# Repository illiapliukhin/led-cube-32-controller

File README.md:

# led-cube-32-controller
Controller system for 1–2 m³ RGB LED cubes built from hanging clocked-pixel strands (HD108, 16-bit, 27 kHz PWM).
- `ARCHITECTURE.md`: v2 architecture (RU summary + EN), with sizing for 32³…128³
- `calc/`: calculation scripts (`rgb_scaling.py`, plus v1 mono calcs)
- `hardware/main_v1`: main board (ESP32-S3 + 8 ports): schematic, PCB, fab
- `hardware/branch_v1`: branch board (16 strands): schematic
- `hardware/archive`: abandoned v1 mono tile (WIP, not DRC clean); `hardware/v15_baseline`: original mono board
- `docs/ARCHITECTURE_v1_mono.md`: phase-1 mono study (superseded)

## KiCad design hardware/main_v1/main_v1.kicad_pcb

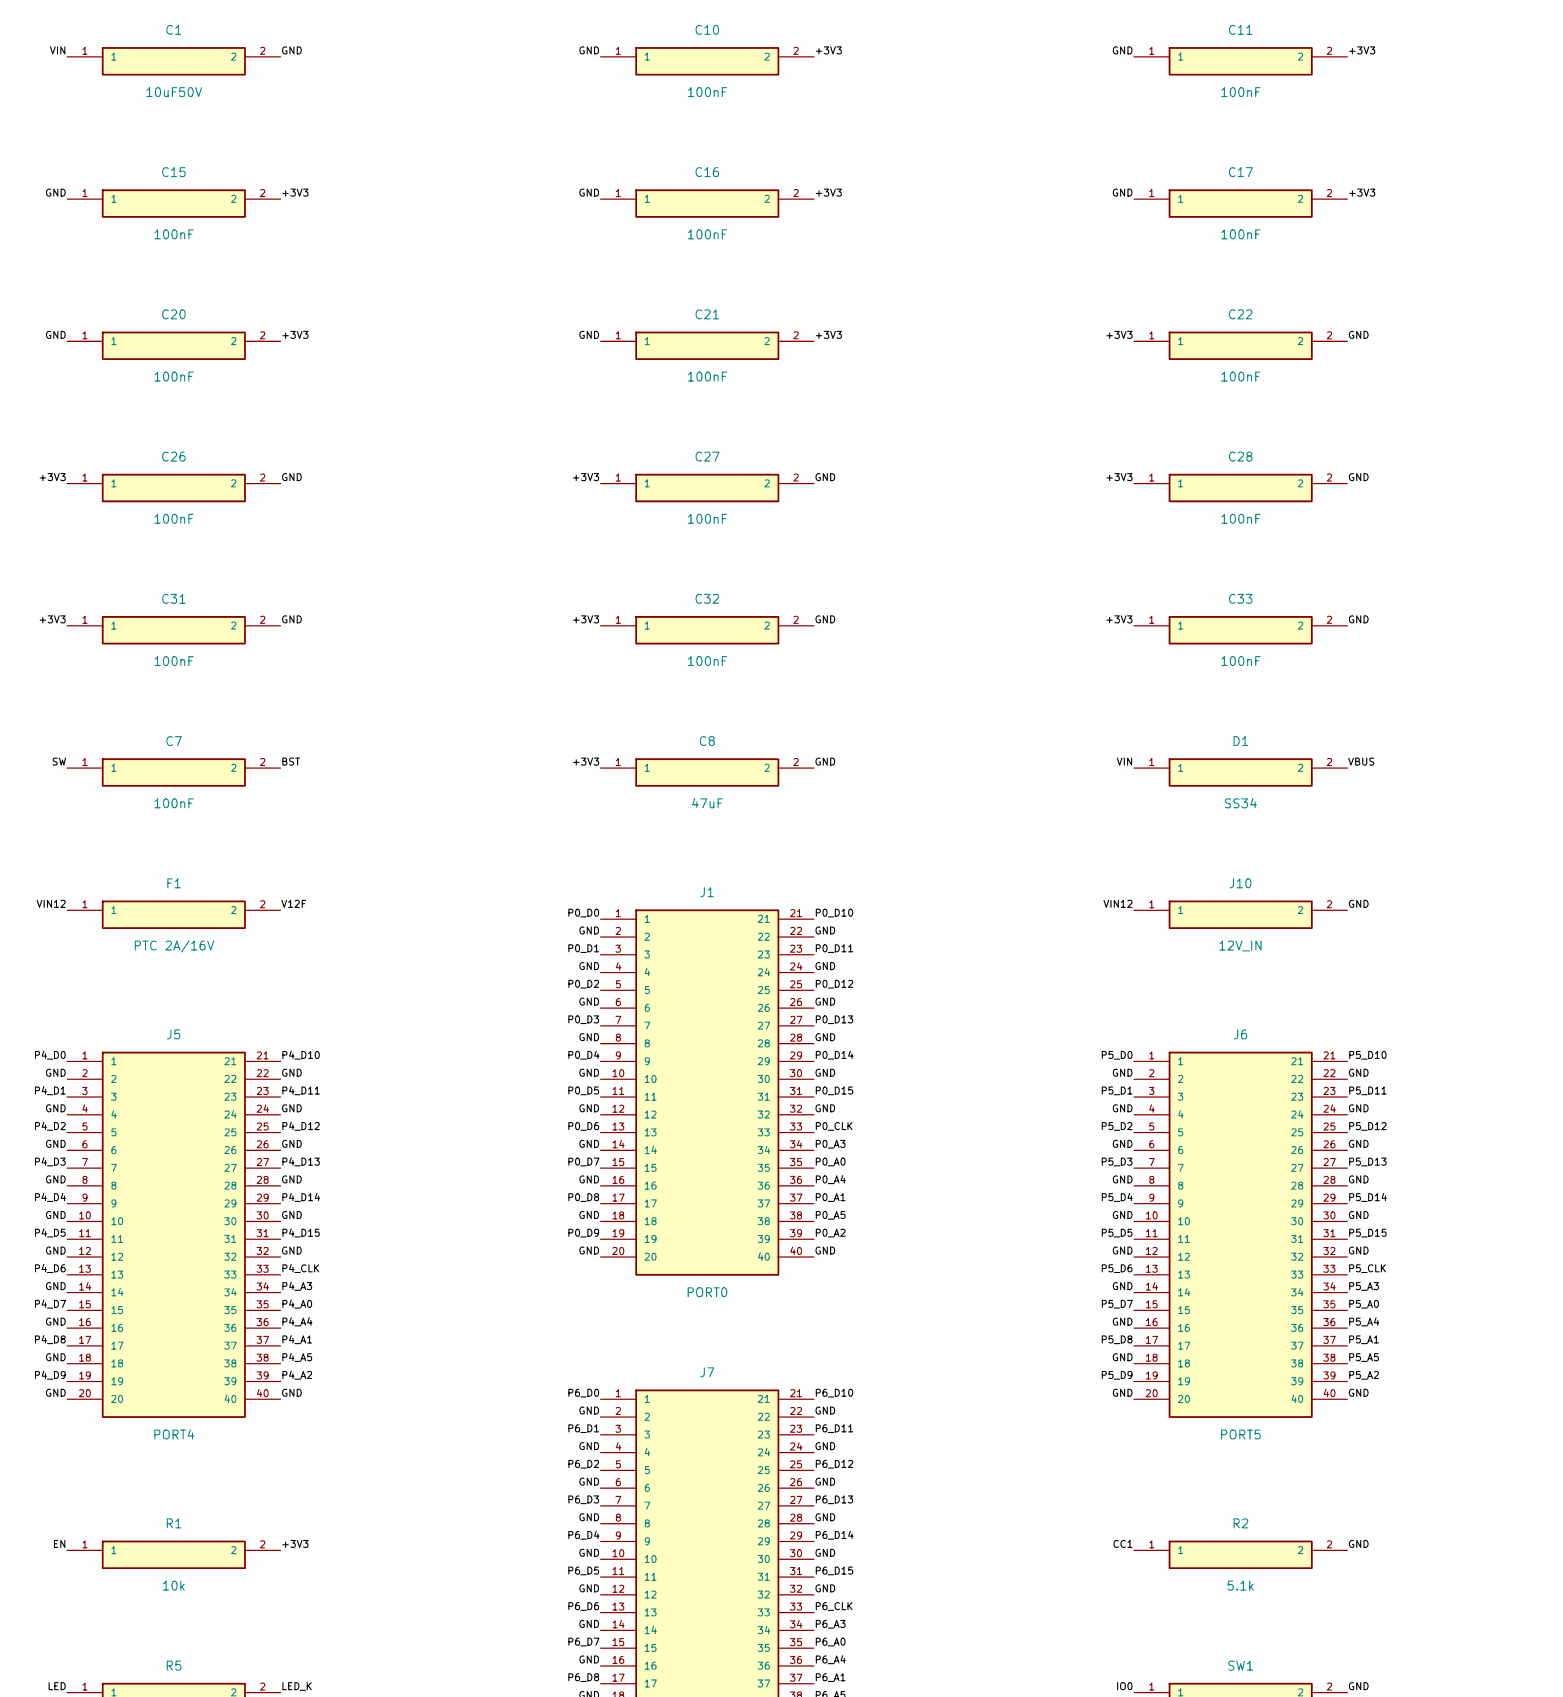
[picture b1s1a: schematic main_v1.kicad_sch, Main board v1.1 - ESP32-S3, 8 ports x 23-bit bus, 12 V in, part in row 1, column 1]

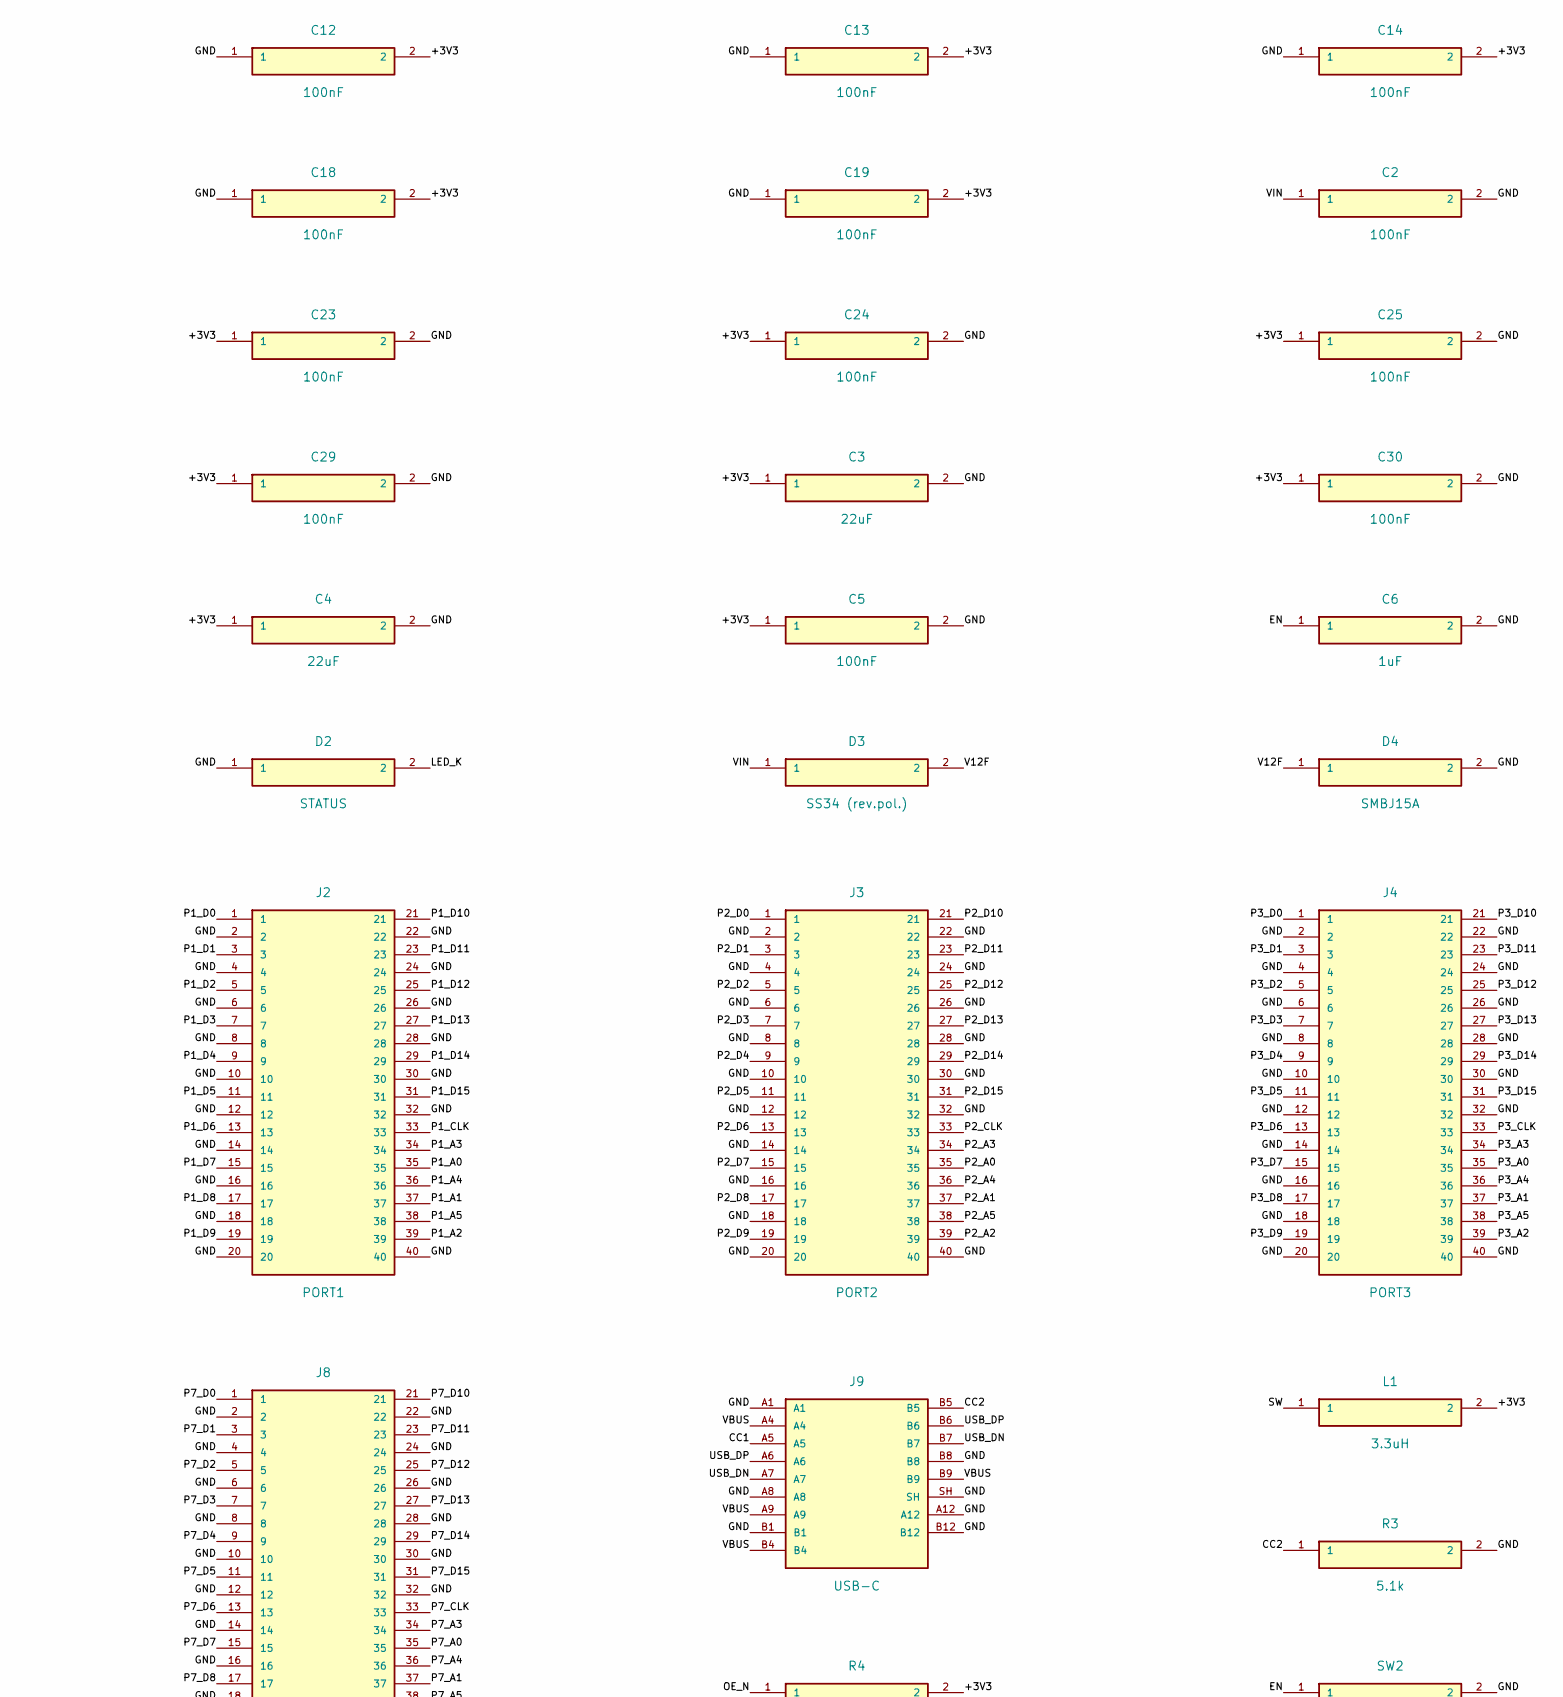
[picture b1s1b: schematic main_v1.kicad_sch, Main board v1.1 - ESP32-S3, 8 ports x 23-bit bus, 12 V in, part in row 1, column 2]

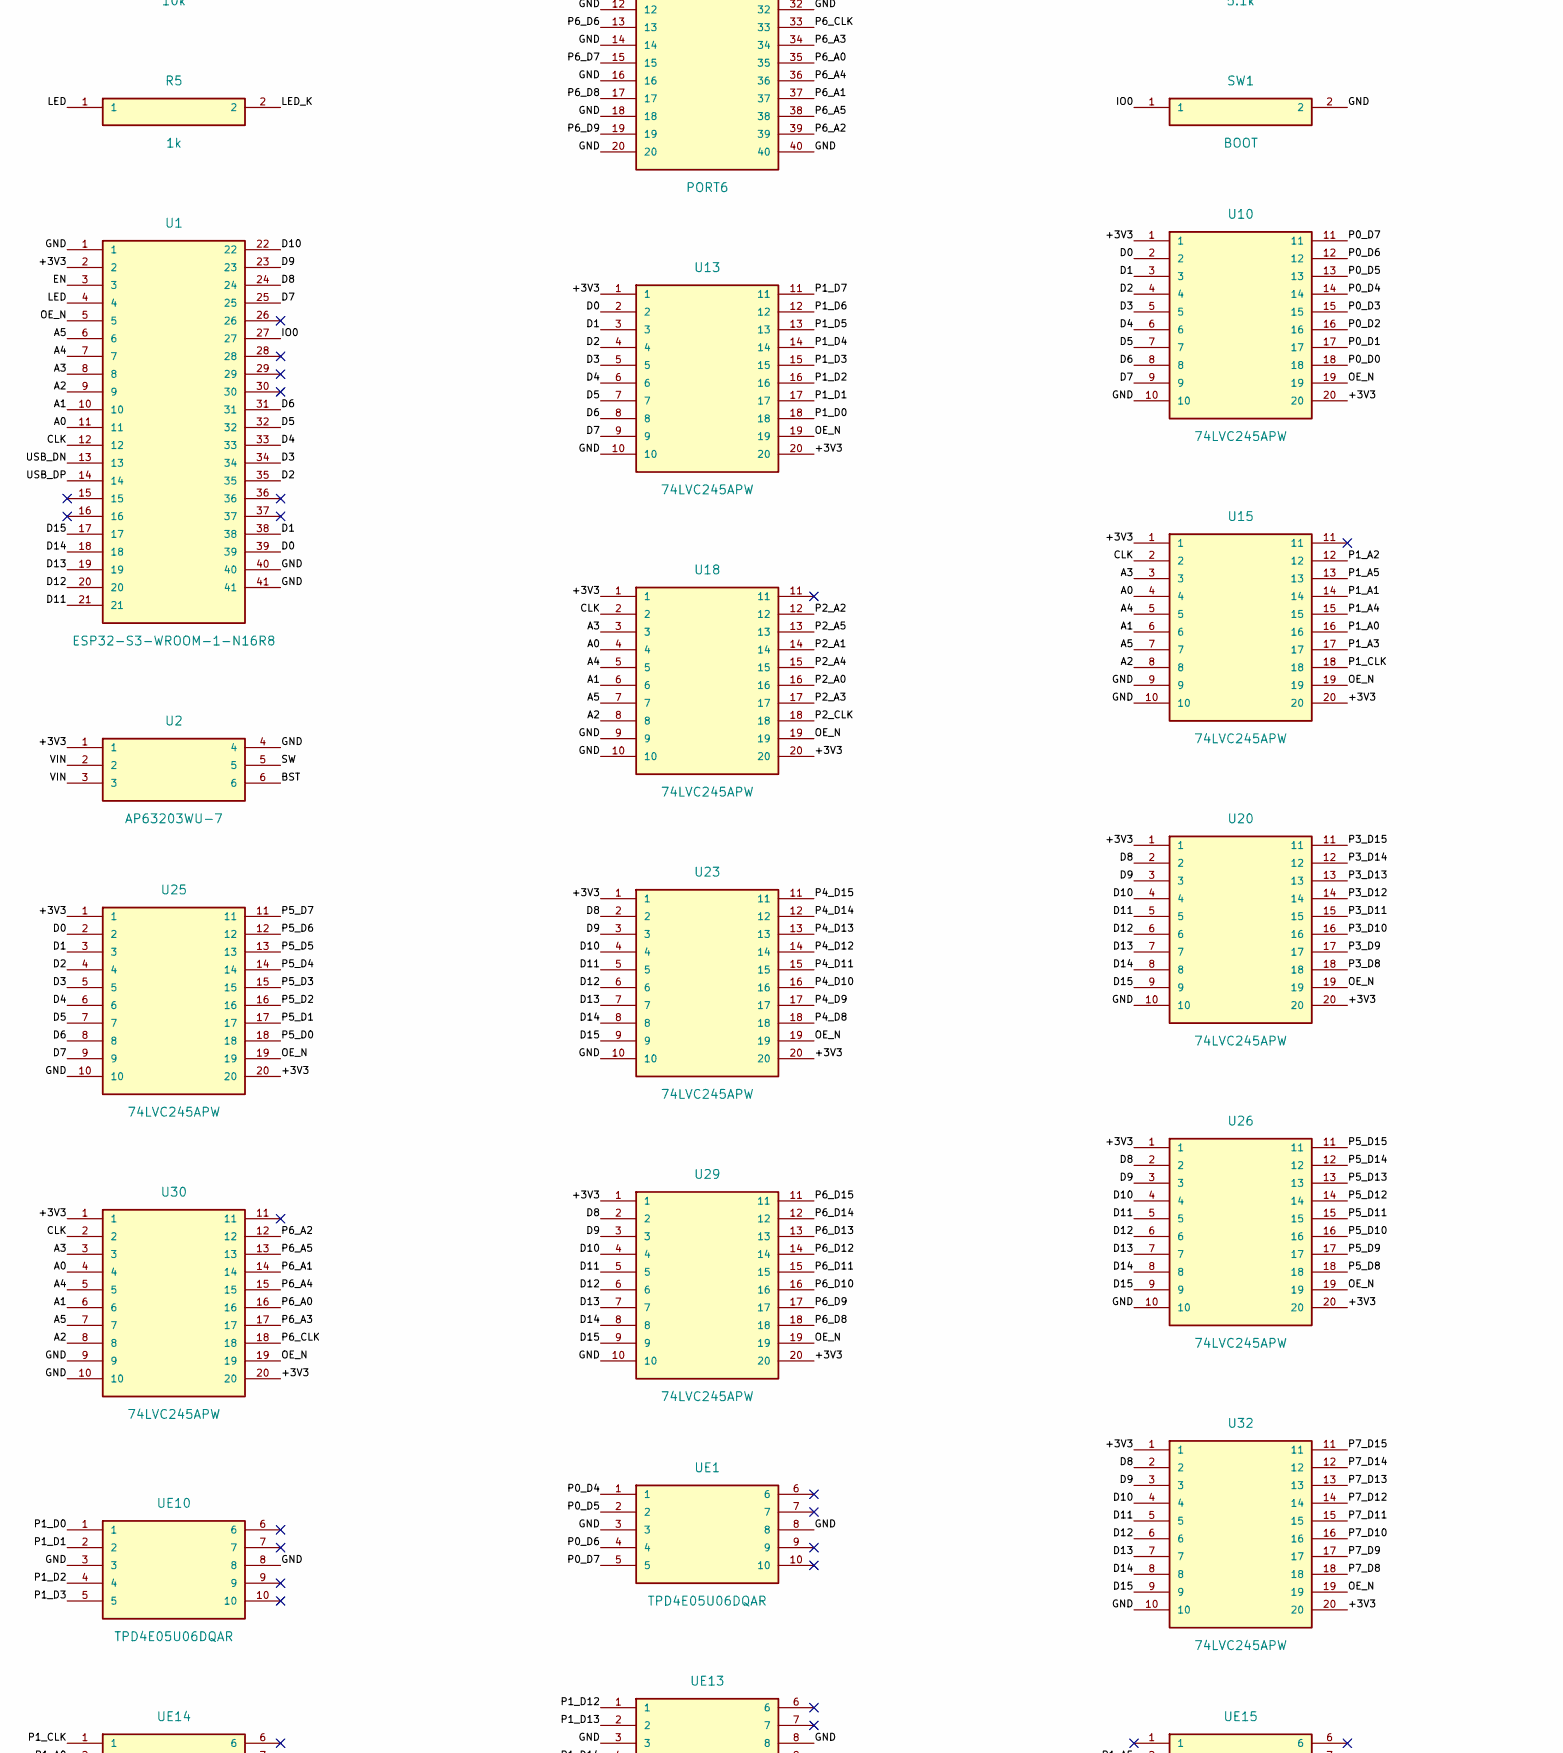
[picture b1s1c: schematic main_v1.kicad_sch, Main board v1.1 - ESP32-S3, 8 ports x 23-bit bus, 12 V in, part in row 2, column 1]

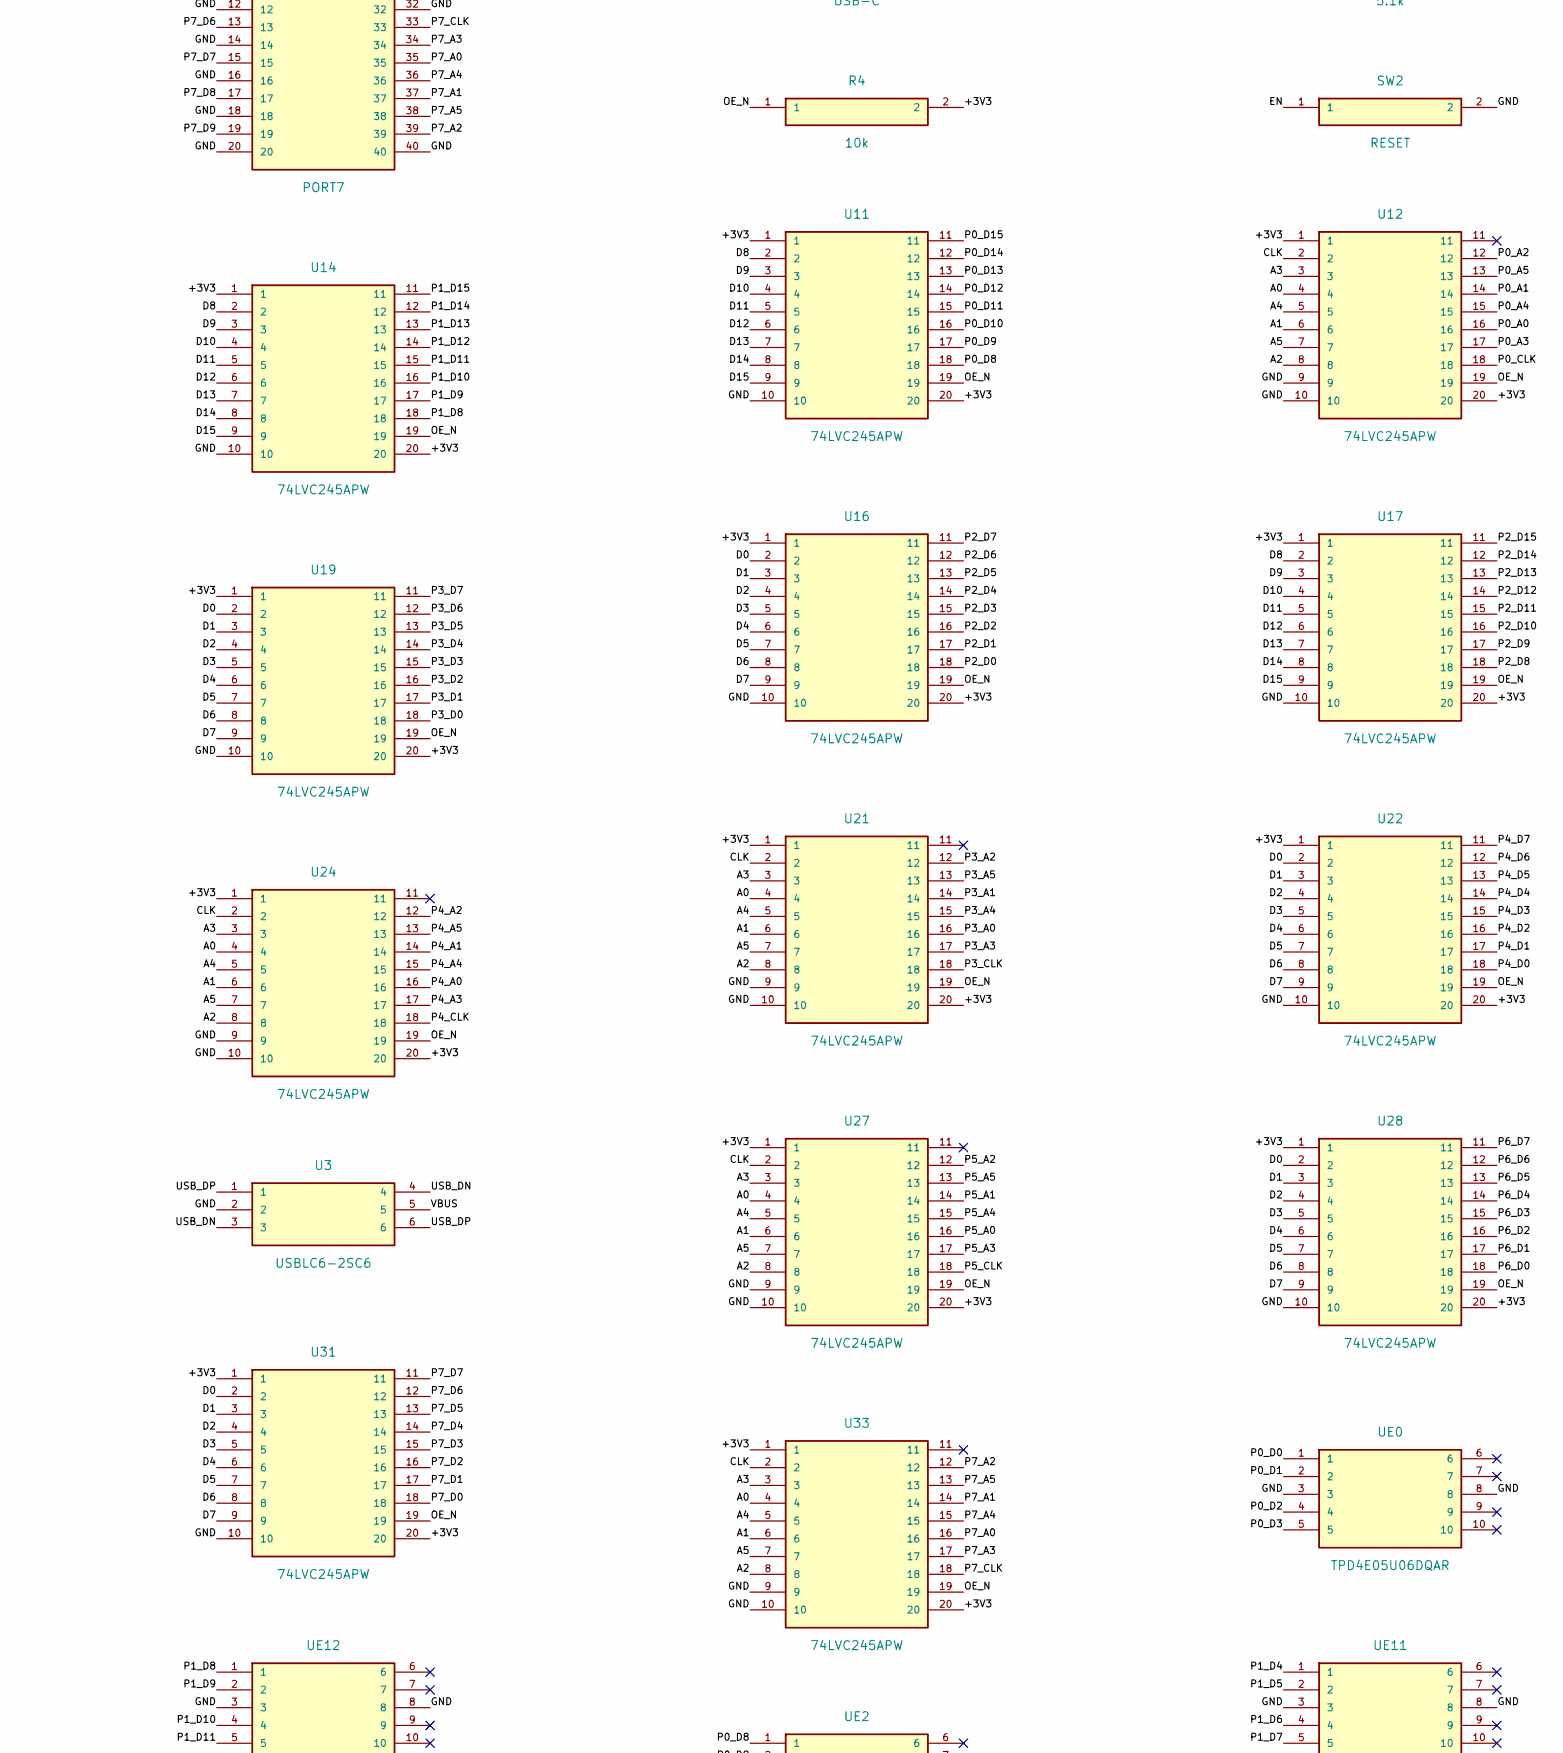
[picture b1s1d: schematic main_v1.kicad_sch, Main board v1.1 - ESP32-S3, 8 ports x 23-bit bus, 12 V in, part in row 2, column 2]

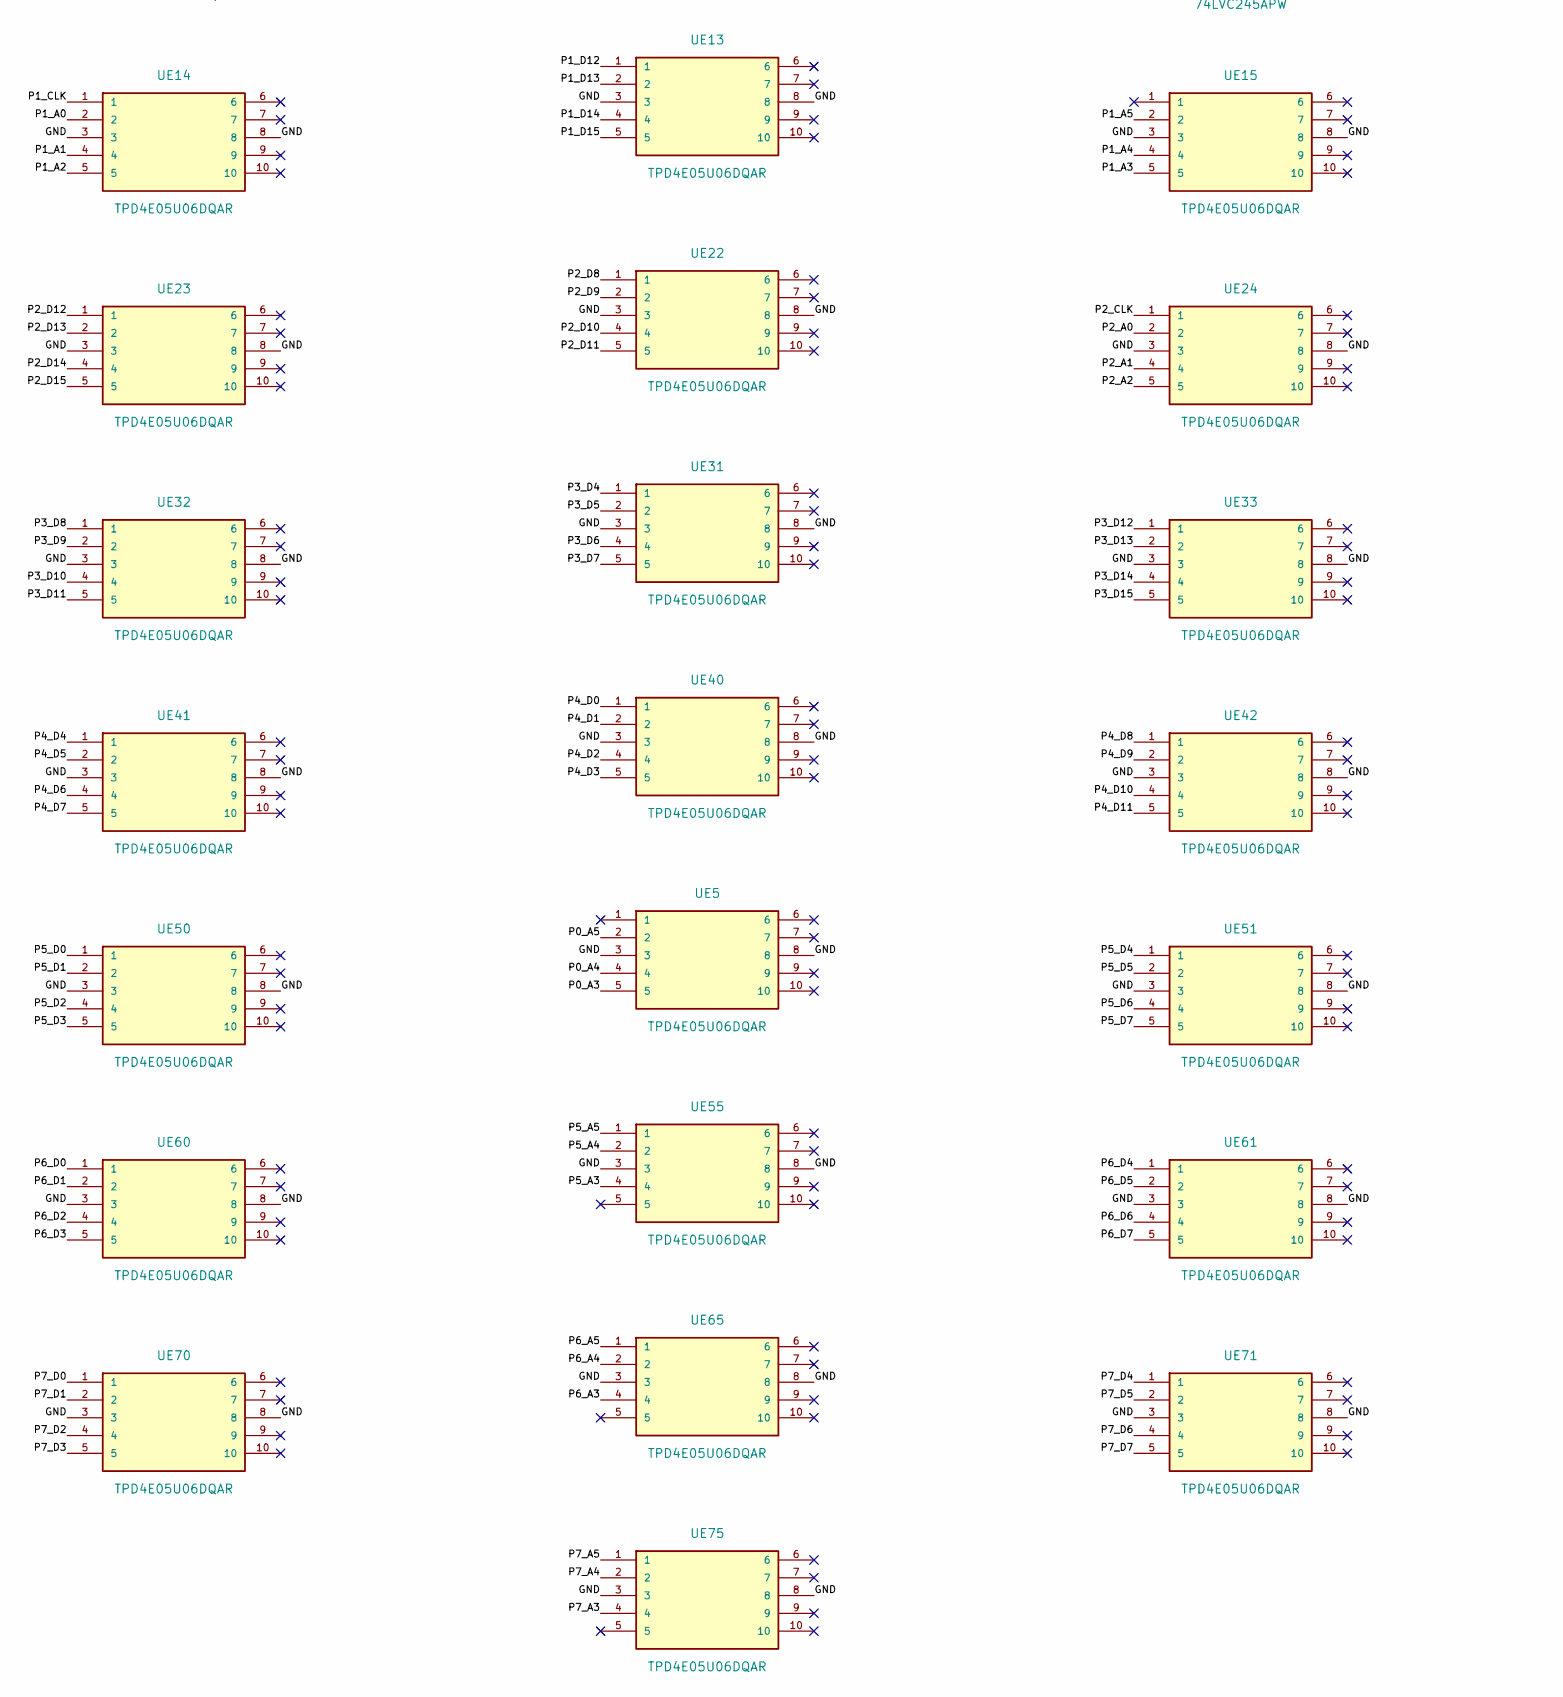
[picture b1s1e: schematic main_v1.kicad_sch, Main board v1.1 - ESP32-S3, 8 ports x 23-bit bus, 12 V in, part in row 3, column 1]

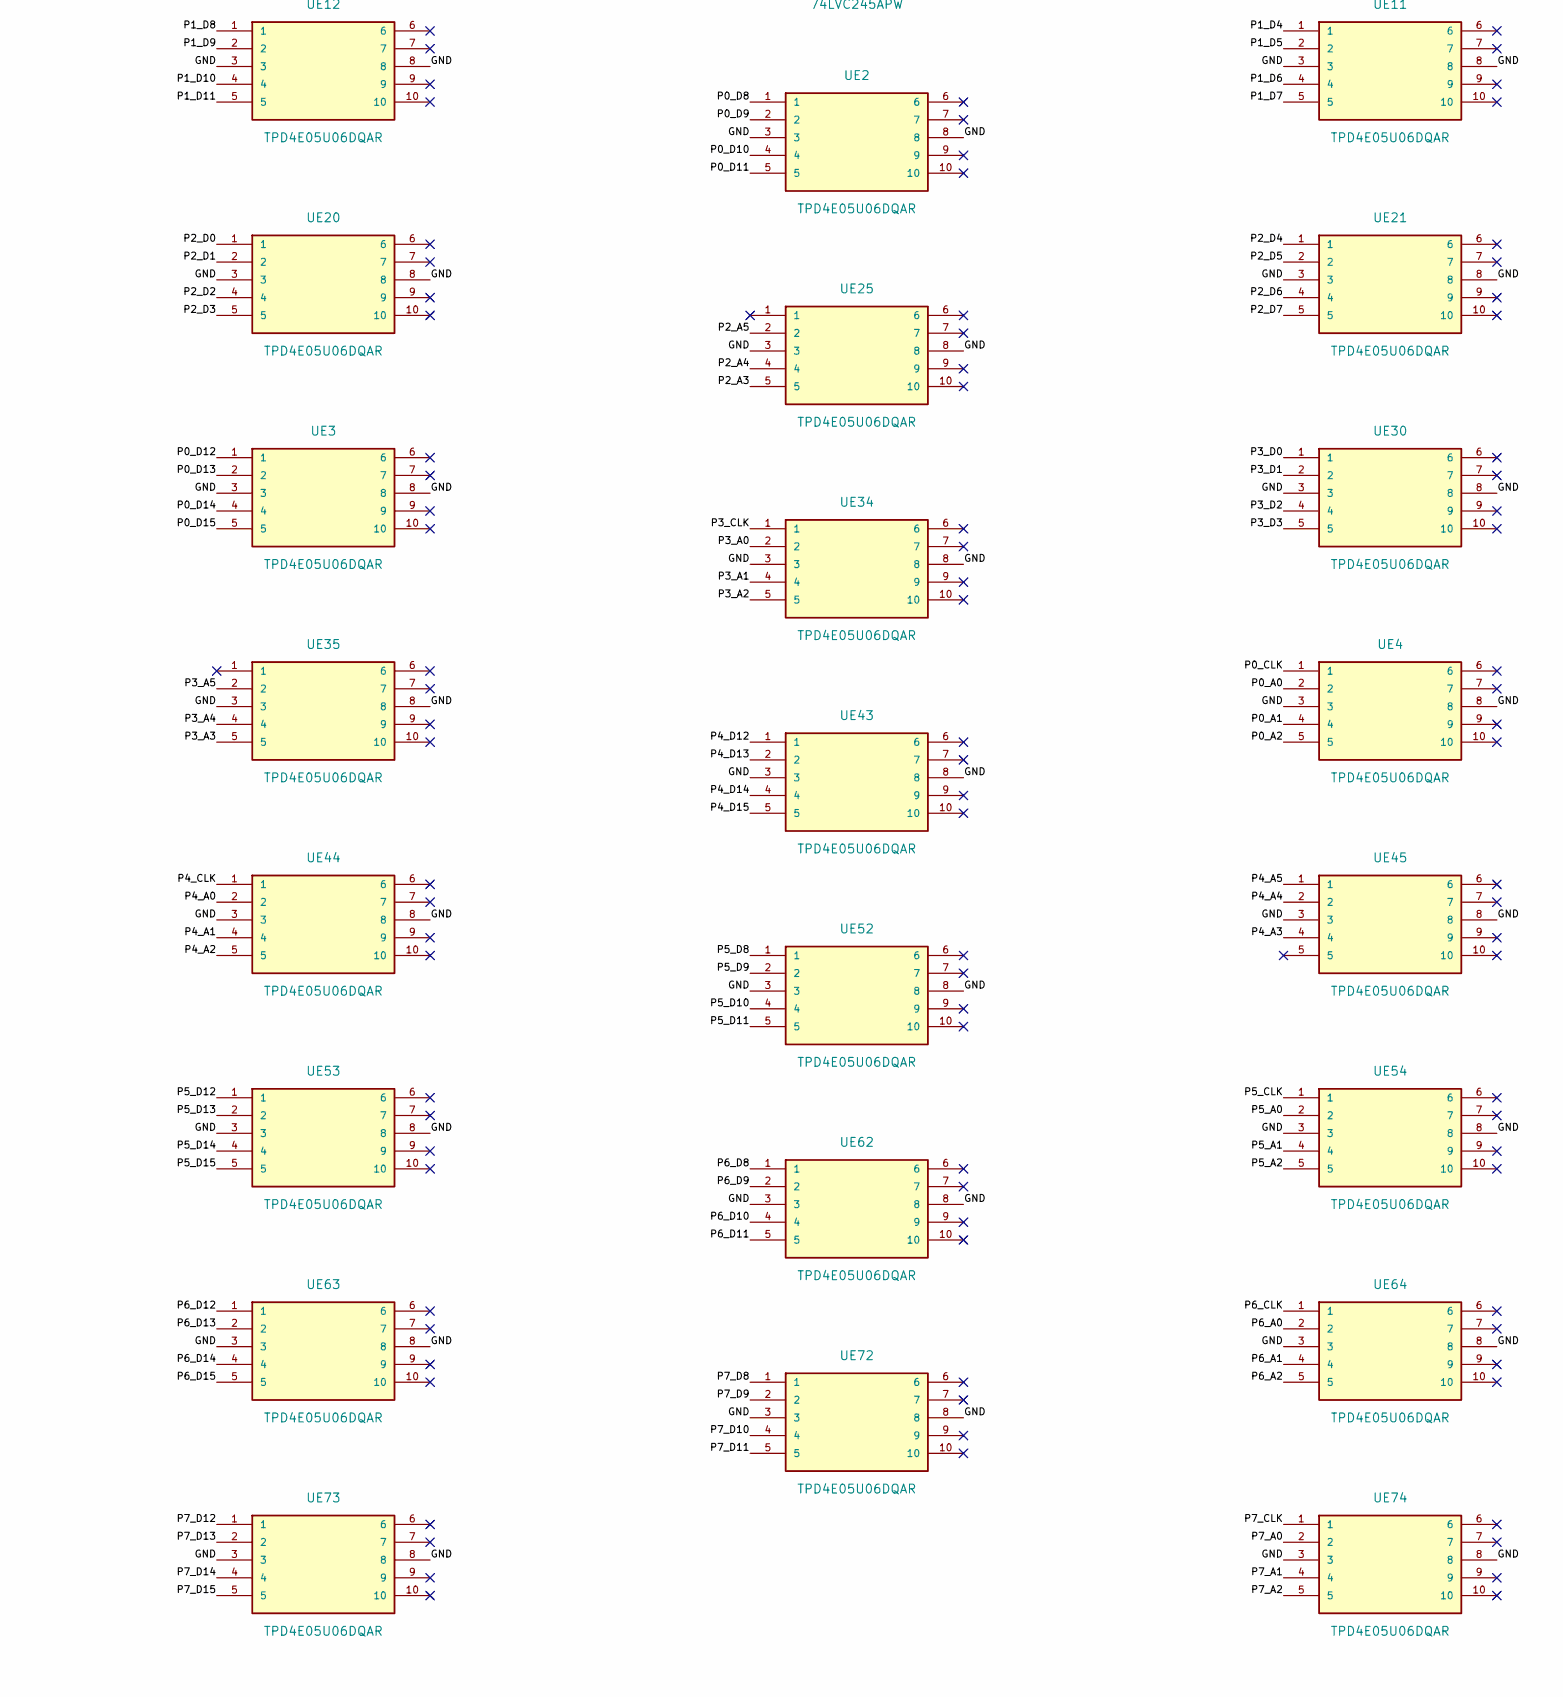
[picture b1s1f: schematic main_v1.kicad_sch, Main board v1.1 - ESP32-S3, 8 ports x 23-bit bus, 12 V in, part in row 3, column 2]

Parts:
C1: 10uF50V; C_1206_3216Metric; MPN CL31A106KBHNNNE; LCSC C13585
C2, C5, C7, C10, C11, C12, C13, C14, C15, C16, C17, C18, C19, C20, C21, C22, C23, C24, C25, C26, C27, C28, C29, C30, C31, C32, C33: 100nF; C_0603_1608Metric; MPN CL10B104KO8NNNC; LCSC C66501
C3, C4: 22uF; C_0603_1608Metric; MPN CL10A226MQ8NRNC; LCSC C59461
C6: 1uF; C_0603_1608Metric; MPN CL10A105KO8NNNC; LCSC C1592
C8: 47uF; C_1210_3225Metric; MPN GRM32ER61C476KE15L; LCSC C77101
D1: SS34; D_SMA; MPN SS34; LCSC C8678
D2: STATUS; LED_0603_1608Metric; MPN KT-0603R; LCSC C2286
D3: SS34 (rev.pol.); D_SMA; MPN SS34; LCSC C8678
D4: SMBJ15A; D_SMB; MPN SMBJ15A; LCSC C83846
F1: PTC 2A/16V; Fuse_1812_4532Metric; MPN SMD1812P200TF16; LCSC C20812
J1: PORT0; IDC-Header_2x20_P2.54mm_Vertical; MPN 2.54-2*20P box header; LCSC C9138
J2: PORT1; IDC-Header_2x20_P2.54mm_Vertical; MPN 2.54-2*20P box header; LCSC C9138
J3: PORT2; IDC-Header_2x20_P2.54mm_Vertical; MPN 2.54-2*20P box header; LCSC C9138
J4: PORT3; IDC-Header_2x20_P2.54mm_Vertical; MPN 2.54-2*20P box header; LCSC C9138
J5: PORT4; IDC-Header_2x20_P2.54mm_Vertical; MPN 2.54-2*20P box header; LCSC C9138
J6: PORT5; IDC-Header_2x20_P2.54mm_Vertical; MPN 2.54-2*20P box header; LCSC C9138
J7: PORT6; IDC-Header_2x20_P2.54mm_Vertical; MPN 2.54-2*20P box header; LCSC C9138
J8: PORT7; IDC-Header_2x20_P2.54mm_Vertical; MPN 2.54-2*20P box header; LCSC C9138
J9: USB-C; USB_C_Receptacle_HRO_TYPE-C-31-M-12; MPN TYPE-C-31-M-12; LCSC C165948
J10: 12V_IN; TerminalBlock_Phoenix_MKDS-1,5-2-5.08_1x02_P5.08mm_Horizont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; MPN WJ500V-5.08-2P; LCSC C8465
L1: 3.3uH; L_Cjiang_FXL0630; MPN FXL0630-3R3-M; LCSC C167219
R1, R4: 10k; R_0603_1608Metric; MPN RC0603FR-0710KL; LCSC C98220
R2, R3: 5.1k; R_0603_1608Metric; MPN 0603WAF5101T5E; LCSC C23186
R5: 1k; R_0603_1608Metric; MPN 0603WAF1001T5E; LCSC C21190
SW1: BOOT; SW_Push_1P1T_XKB_TS-1187A; MPN TS-1187A-B-A-B; LCSC C318884
SW2: RESET; SW_Push_1P1T_XKB_TS-1187A; MPN TS-1187A-B-A-B; LCSC C318884
U1: ESP32-S3-WROOM-1-N16R8; ESP32-S3-WROOM-1; MPN ESP32-S3-WROOM-1-N16R8; LCSC C2913202
U2: AP63203WU-7; TSOT-23-6; MPN AP63203WU-7; LCSC C780769
U3: USBLC6-2SC6; SOT-23-6; MPN USBLC6-2SC6; LCSC C2827654
U10, U11, U12, U13, U14, U15, U16, U17, U18, U19, U20, U21, U22, U23, U24, U25, U26, U27, U28, U29, U30, U31, U32, U33: 74LVC245APW; TSSOP-20_4.4x6.5mm_P0.65mm; MPN 74LVC245APW,118; LCSC C6082
UE0, UE1, UE2, UE3, UE4, UE5, UE10, UE11, UE12, UE13, UE14, UE15, UE20, UE21, UE22, UE23, UE24, UE25, UE30, UE31, UE32, UE33, UE34, UE35, UE40, UE41, UE42, UE43, UE44, UE45, UE50, UE51, UE52, UE53, UE54, UE55, UE60, UE61, UE62, UE63, UE64, UE65, UE70, UE71, UE72, UE73, UE74, UE75: TPD4E05U06DQAR; USON-10_2.5x1.0mm_P0.5mm; MPN TPD4E05U06DQAR; LCSC C138714

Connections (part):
/+3V3: C3.1, C4.1, C5.1, C8.1, C10.2, C11.2, C12.2, C13.2, C14.2, C15.2, C16.2, C17.2, C18.2, C19.2, C20.2, C21.2, C22.1, C23.1, C24.1, C25.1, C26.1, C27.1, C28.1, C29.1, C30.1, C31.1, C32.1, C33.1, L1.2, R1.2, R4.2, U1.2, U2.1, U10.1, U10.20, U11.1, U11.20, U12.1, U12.20, U13.1, U13.20, U14.1, U14.20, U15.1, U15.20, U16.1, U16.20, U17.1, U17.20, U18.1, U18.20, U19.1, U19.20, U20.1, U20.20, U21.1, U21.20, U22.1, U22.20, U23.1, U23.20, U24.1, U24.20, U25.1, U25.20, U26.1, U26.20, U27.1, U27.20, U28.1, U28.20, U29.1, U29.20, U30.1, U30.20, U31.1, U31.20, U32.1, U32.20, U33.1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
/A0: U1.11, U12.4, U15.4, U18.4, U21.4, U24.4, U27.4, U30.4, U33.4
/A1: U1.10, U12.6, U15.6, U18.6, U21.6, U24.6, U27.6, U30.6, U33.6
/A2: U1.9, U12.8, U15.8, U18.8, U21.8, U24.8, U27.8, U30.8, U33.8
/A3: U1.8, U12.3, U15.3, U18.3, U21.3, U24.3, U27.3, U30.3, U33.3
/A4: U1.7, U12.5, U15.5, U18.5, U21.5, U24.5, U27.5, U30.5, U33.5
/A5: U1.6, U12.7, U15.7, U18.7, U21.7, U24.7, U27.7, U30.7, U33.7
/BST: C7.2, U2.6
/CC1: J9.A5, R2.1
/CC2: J9.B5, R3.1
/CLK: U1.12, U12.2, U15.2, U18.2, U21.2, U24.2, U27.2, U30.2, U33.2
/D0: U1.39, U10.2, U13.2, U16.2, U19.2, U22.2, U25.2, U28.2, U31.2
/D1: U1.38, U10.3, U13.3, U16.3, U19.3, U22.3, U25.3, U28.3, U31.3
/D2: U1.35, U10.4, U13.4, U16.4, U19.4, U22.4, U25.4, U28.4, U31.4
/D3: U1.34, U10.5, U13.5, U16.5, U19.5, U22.5, U25.5, U28.5, U31.5
/D4: U1.33, U10.6, U13.6, U16.6, U19.6, U22.6, U25.6, U28.6, U31.6
/D5: U1.32, U10.7, U13.7, U16.7, U19.7, U22.7, U25.7, U28.7, U31.7
/D6: U1.31, U10.8, U13.8, U16.8, U19.8, U22.8, U25.8, U28.8, U31.8
/D7: U1.25, U10.9, U13.9, U16.9, U19.9, U22.9, U25.9, U28.9, U31.9
/D8: U1.24, U11.2, U14.2, U17.2, U20.2, U23.2, U26.2, U29.2, U32.2
/D9: U1.23, U11.3, U14.3, U17.3, U20.3, U23.3, U26.3, U29.3, U32.3
/D10: U1.22, U11.4, U14.4, U17.4, U20.4, U23.4, U26.4, U29.4, U32.4
/D11: U1.21, U11.5, U14.5, U17.5, U20.5, U23.5, U26.5, U29.5, U32.5
/D12: U1.20, U11.6, U14.6, U17.6, U20.6, U23.6, U26.6, U29.6, U32.6
/D13: U1.19, U11.7, U14.7, U17.7, U20.7, U23.7, U26.7, U29.7, U32.7
/D14: U1.18, U11.8, U14.8, U17.8, U20.8, U23.8, U26.8, U29.8, U32.8
/D15: U1.17, U11.9, U14.9, U17.9, U20.9, U23.9, U26.9, U29.9, U32.9
/EN: C6.1, R1.1, SW2.1, U1.3
/GND: C1.2, C2.2, C3.2, C4.2, C5.2, C6.2, C8.2, C10.1, C11.1, C12.1, C13.1, C14.1, C15.1, C16.1, C17.1, C18.1, C19.1, C20.1, C21.1, C22.2, C23.2, C24.2, C25.2, C26.2, C27.2, C28.2, C29.2, C30.2, C31.2, C32.2, C33.2, D2.1, D4.2, J1.2, J1.4, J1.6, J1.8, J1.10, J1.12, J1.14, J1.16, J1.18, J1.20, J1.22, J1.24, J1.26, J1.28, J1.30, J1.32, J1.40, J2.2, J2.4, J2.6, J2.8, J2.10, J2.12, J2.14, J2.16, J2.18, J2.20, J2.22, J2.24, J2.26, J2.28, J2.30, J2.32, J2.40, J3.2, J3.4, J3.6, J3.8, J3.10, J3.12, J3.14, J3.16, J3.18, J3.20, J3.22, J3.24, J3.26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
/IO0: SW1.1, U1.27
/LED: R5.1, U1.4
/LED_K: D2.2, R5.2
/OE_N: R4.1, U1.5, U10.19, U11.19, U12.19, U13.19, U14.19, U15.19, U16.19, U17.19, U18.19, U19.19, U20.19, U21.19, U22.19, U23.19, U24.19, U25.19, U26.19, U27.19, U28.19, U29.19, U30.19, U31.19, U32.19, U33.19
/P0_A0: J1.35, U12.16, UE4.2
/P0_A1: J1.37, U12.14, UE4.4
/P0_A2: J1.39, U12.12, UE4.5
/P0_A3: J1.34, U12.17, UE5.5
/P0_A4: J1.36, U12.15, UE5.4
/P0_A5: J1.38, U12.13, UE5.2
/P0_CLK: J1.33, U12.18, UE4.1
/P0_D0: J1.1, U10.18, UE0.1
/P0_D1: J1.3, U10.17, UE0.2
/P0_D2: J1.5, U10.16, UE0.4
/P0_D3: J1.7, U10.15, UE0.5
/P0_D4: J1.9, U10.14, UE1.1
/P0_D5: J1.11, U10.13, UE1.2
/P0_D6: J1.13, U10.12, UE1.4
/P0_D7: J1.15, U10.11, UE1.5
/P0_D8: J1.17, U11.18, UE2.1
/P0_D9: J1.19, U11.17, UE2.2
/P0_D10: J1.21, U11.16, UE2.4
/P0_D11: J1.23, U11.15, UE2.5
/P0_D12: J1.25, U11.14, UE3.1
/P0_D13: J1.27, U11.13, UE3.2
/P0_D14: J1.29, U11.12, UE3.4
/P0_D15: J1.31, U11.11, UE3.5
/P1_A0: J2.35, U15.16, UE14.2
/P1_A1: J2.37, U15.14, UE14.4
/P1_A2: J2.39, U15.12, UE14.5
/P1_A3: J2.34, U15.17, UE15.5
/P1_A4: J2.36, U15.15, UE15.4
/P1_A5: J2.38, U15.13, UE15.2
/P1_CLK: J2.33, U15.18, UE14.1
/P1_D0: J2.1, U13.18, UE10.1
/P1_D1: J2.3, U13.17, UE10.2
/P1_D2: J2.5, U13.16, UE10.4
/P1_D3: J2.7, U13.15, UE10.5
/P1_D4: J2.9, U13.14, UE11.1
/P1_D5: J2.11, U13.13, UE11.2
/P1_D6: J2.13, U13.12, UE11.4
/P1_D7: J2.15, U13.11, UE11.5
/P1_D8: J2.17, U14.18, UE12.1
/P1_D9: J2.19, U14.17, UE12.2
/P1_D10: J2.21, U14.16, UE12.4
/P1_D11: J2.23, U14.15, UE12.5
/P1_D12: J2.25, U14.14, UE13.1
/P1_D13: J2.27, U14.13, UE13.2
/P1_D14: J2.29, U14.12, UE13.4
/P1_D15: J2.31, U14.11, UE13.5
/P2_A0: J3.35, U18.16, UE24.2
/P2_A1: J3.37, U18.14, UE24.4
/P2_A2: J3.39, U18.12, UE24.5
/P2_A3: J3.34, U18.17, UE25.5
/P2_A4: J3.36, U18.15, UE25.4
/P2_A5: J3.38, U18.13, UE25.2
/P2_CLK: J3.33, U18.18, UE24.1
/P2_D0: J3.1, U16.18, UE20.1
/P2_D1: J3.3, U16.17, UE20.2
/P2_D2: J3.5, U16.16, UE20.4
/P2_D3: J3.7, U16.15, UE20.5
/P2_D4: J3.9, U16.14, UE21.1
/P2_D5: J3.11, U16.13, UE21.2
/P2_D6: J3.13, U16.12, UE21.4
/P2_D7: J3.15, U16.11, UE21.5
/P2_D8: J3.17, U17.18, UE22.1
/P2_D9: J3.19, U17.17, UE22.2
/P2_D10: J3.21, U17.16, UE22.4
/P2_D11: J3.23, U17.15, UE22.5
/P2_D12: J3.25, U17.14, UE23.1
/P2_D13: J3.27, U17.13, UE23.2
/P2_D14: J3.29, U17.12, UE23.4
/P2_D15: J3.31, U17.11, UE23.5
/P3_A0: J4.35, U21.16, UE34.2
/P3_A1: J4.37, U21.14, UE34.4
/P3_A2: J4.39, U21.12, UE34.5
/P3_A3: J4.34, U21.17, UE35.5
/P3_A4: J4.36, U21.15, UE35.4
/P3_A5: J4.38, U21.13, UE35.2
/P3_CLK: J4.33, U21.18, UE34.1
/P3_D0: J4.1, U19.18, UE30.1
/P3_D1: J4.3, U19.17, UE30.2
/P3_D2: J4.5, U19.16, UE30.4
/P3_D3: J4.7, U19.15, UE30.5
/P3_D4: J4.9, U19.14, UE31.1
/P3_D5: J4.11, U19.13, UE31.2
/P3_D6: J4.13, U19.12, UE31.4
/P3_D7: J4.15, U19.11, UE31.5
/P3_D8: J4.17, U20.18, UE32.1
/P3_D9: J4.19, U20.17, UE32.2
/P3_D10: J4.21, U20.16, UE32.4
/P3_D11: J4.23, U20.15, UE32.5
/P3_D12: J4.25, U20.14, UE33.1
/P3_D13: J4.27, U20.13, UE33.2
/P3_D14: J4.29, U20.12, UE33.4
/P3_D15: J4.31, U20.11, UE33.5
/P4_A0: J5.35, U24.16, UE44.2
/P4_A1: J5.37, U24.14, UE44.4
/P4_A2: J5.39, U24.12, UE44.5
/P4_A3: J5.34, U24.17, UE45.4
/P4_A4: J5.36, U24.15, UE45.2
/P4_A5: J5.38, U24.13, UE45.1
/P4_CLK: J5.33, U24.18, UE44.1
/P4_D0: J5.1, U22.18, UE40.1
/P4_D1: J5.3, U22.17, UE40.2
/P4_D2: J5.5, U22.16, UE40.4
/P4_D3: J5.7, U22.15, UE40.5
/P4_D4: J5.9, U22.14, UE41.1
/P4_D5: J5.11, U22.13, UE41.2
/P4_D6: J5.13, U22.12, UE41.4
/P4_D7: J5.15, U22.11, UE41.5
/P4_D8: J5.17, U23.18, UE42.1
/P4_D9: J5.19, U23.17, UE42.2
/P4_D10: J5.21, U23.16, UE42.4
/P4_D11: J5.23, U23.15, UE42.5
/P4_D12: J5.25, U23.14, UE43.1
/P4_D13: J5.27, U23.13, UE43.2
/P4_D14: J5.29, U23.12, UE43.4
/P4_D15: J5.31, U23.11, UE43.5
/P5_A0: J6.35, U27.16, UE54.2
/P5_A1: J6.37, U27.14, UE54.4
/P5_A2: J6.39, U27.12, UE54.5
/P5_A3: J6.34, U27.17, UE55.4
/P5_A4: J6.36, U27.15, UE55.2
/P5_A5: J6.38, U27.13, UE55.1
/P5_CLK: J6.33, U27.18, UE54.1
/P5_D0: J6.1, U25.18, UE50.1
/P5_D1: J6.3, U25.17, UE50.2
/P5_D2: J6.5, U25.16, UE50.4
/P5_D3: J6.7, U25.15, UE50.5
/P5_D4: J6.9, U25.14, UE51.1
/P5_D5: J6.11, U25.13, UE51.2
/P5_D6: J6.13, U25.12, UE51.4
/P5_D7: J6.15, U25.11, UE51.5
/P5_D8: J6.17, U26.18, UE52.1
/P5_D9: J6.19, U26.17, UE52.2
/P5_D10: J6.21, U26.16, UE52.4
/P5_D11: J6.23, U26.15, UE52.5
/P5_D12: J6.25, U26.14, UE53.1
/P5_D13: J6.27, U26.13, UE53.2
/P5_D14: J6.29, U26.12, UE53.4
/P5_D15: J6.31, U26.11, UE53.5
/P6_A0: J7.35, U30.16, UE64.2
/P6_A1: J7.37, U30.14, UE64.4
/P6_A2: J7.39, U30.12, UE64.5
/P6_A3: J7.34, U30.17, UE65.4
/P6_A4: J7.36, U30.15, UE65.2
/P6_A5: J7.38, U30.13, UE65.1
/P6_CLK: J7.33, U30.18, UE64.1
/P6_D0: J7.1, U28.18, UE60.1
/P6_D1: J7.3, U28.17, UE60.2
/P6_D2: J7.5, U28.16, UE60.4
/P6_D3: J7.7, U28.15, UE60.5
/P6_D4: J7.9, U28.14, UE61.1
/P6_D5: J7.11, U28.13, UE61.2
/P6_D6: J7.13, U28.12, UE61.4
/P6_D7: J7.15, U28.11, UE61.5
/P6_D8: J7.17, U29.18, UE62.1
/P6_D9: J7.19, U29.17, UE62.2
/P6_D10: J7.21, U29.16, UE62.4
/P6_D11: J7.23, U29.15, UE62.5
/P6_D12: J7.25, U29.14, UE63.1
/P6_D13: J7.27, U29.13, UE63.2
/P6_D14: J7.29, U29.12, UE63.4
/P6_D15: J7.31, U29.11, UE63.5
/P7_A0: J8.35, U33.16, UE74.2
/P7_A1: J8.37, U33.14, UE74.4
/P7_A2: J8.39, U33.12, UE74.5
/P7_A3: J8.34, U33.17, UE75.4
/P7_A4: J8.36, U33.15, UE75.2
/P7_A5: J8.38, U33.13, UE75.1
/P7_CLK: J8.33, U33.18, UE74.1
/P7_D0: J8.1, U31.18, UE70.1
/P7_D1: J8.3, U31.17, UE70.2
/P7_D2: J8.5, U31.16, UE70.4
/P7_D3: J8.7, U31.15, UE70.5
/P7_D4: J8.9, U31.14, UE71.1
/P7_D5: J8.11, U31.13, UE71.2
/P7_D6: J8.13, U31.12, UE71.4
/P7_D7: J8.15, U31.11, UE71.5
/P7_D8: J8.17, U32.18, UE72.1
/P7_D9: J8.19, U32.17, UE72.2
/P7_D10: J8.21, U32.16, UE72.4
/P7_D11: J8.23, U32.15, UE72.5
/P7_D12: J8.25, U32.14, UE73.1
/P7_D13: J8.27, U32.13, UE73.2
/P7_D14: J8.29, U32.12, UE73.4
/P7_D15: J8.31, U32.11, UE73.5
/SW: C7.1, L1.1, U2.5
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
